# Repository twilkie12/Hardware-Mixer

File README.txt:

As a disclaimer, I am an amateur at programming and hardware design and so cannot guarantee any of this will work for you.
Will only work for Windows 10 but the hardware could easily be used with an equivalent program on Linux.
It's a bit buggy and probably not written to any decent standard but it is what it is.
This document is less of a README and more of a loose, constantly changing list of things I need to do, need to fix, want to add, need 
to look into or just think some time in the future could be interesting to look at. As such it is basically a brain dump and not
hugely important; nothing past the second paragraph will be useful for actually creating/setting up the board.
Will be adding a plastic enclosure at some point, probably 3D printed base with acrylic top.
Ask and I can send you a (possibly assembled for a fee) PCB for cost + shipping, ostensibly to test and help with prototyping but with 
no obligation to do so however any help adding to or fixing things would be appreciated.
I am open to any and all feedback.

If you decide to get the PCB manufactured yourself and put it all together yourself then some notes:

	- The Kicad board routing is currently broken because of the way I did the pours. Rebuilding it will give you a single 5V pour
	  on the top and a single GND pour on the bottom (maybe, your milage may vary). This is an issue because there is supposed to be 
	  THREE small GND zones on the top surface, one each on the right of the PIC16f15323's and one off the GND pin of the micro-usb
	  connector with a single 5V zone on the rest of the surface. I will at some stage fix this but I have already ordered the
	  boards and the file broke afterwards so it is not a top priority for me.
	- The python script looks for a specific serial number on a USB device and then trys to connect to that. You will need to use
	  a CH340B as this is allows you to change the EEPROM and write the serial number to the chip. The software and drivers to
	  do this and use CH340 chips are ahead but I will say that while the drivers are from the manufactuers site the CFG program is
	  not, with the most official looking download being from the WCH forum; and I really cannot condone downloading a random .rar
	  from unknown sources. I have not downloaded the CFG from this source instead I initially found it only on a random chinese
	  filehosting site which is probably even worse.
	  (Drivers: http://www.wch.cn/download/CH341SER_EXE.html, and the program used to configure the EEPROM:
	  http://wch.cn/index.php/bbs/thread-64449-2.html -- Called CH340CFG, there are multiple sources available through google). 
	- As a warning you ONLY want to change the serial number on the chipe, changing VID, or PID WILL make the drivers stop working
	  until you manually reassign the driver to the device, not recommended if you do not know your way around your PC.
	- You will need an Arduino, USBasp or similar to burn the Arduino bootloader to the ATMEGA 168 with Arduino IDE as well as 
	  needing a PICKIT and ZIF socket to flash the PIC's. If you are so inclined adding ISP points to the PCB to flash the PIC's
	  would be very simple and I will likely add them in the next revision.

Idea is for a board with 2 rotary encoders (tried pots, didn't really work nicely), a slide pot and 16x2 LCD screen with PCF85741 i2c
backpack used to control the windows 10 volume mixer program with hardware.

Controls 2 programs volume at a time, with the name of the active programs given on the LCD screen and the active programs changed by
pressing the rotary encoder button. Master volume is controlled by slider.

Uses Atmega 168 (could use 328 easily) with arduino to run the board with PIC16f15323's reading the rotary encoders (Fattoresaimon's
i2cencoder project, https://github.com/Fattoresaimon/i2cencoder). 

AndreMiras's pycaw library used to control Windows volume mixer (https://github.com/AndreMiras/pycaw). 

Francisco Malpartida's i2cliquidcrystal library for arduino (https://bitbucket.org/fmalpartida/new-liquidcrystal/wiki/Home) 
(Need to make sure you have the right one as there are quite a few libraries with the same names with slightly different
implementations)

Uses CH340B USB-Serial chip for it's EEPROM to allow python script to recognise board (http://www.wch.cn/products/CH340.html),
(https://lcsc.com/product-detail/USB_CH340B_C81010.html).

To do:

Biggest thing is to make LCD mount on the pcb directly rather then through floating
Remove i2c backpack and just communicate directly using pins on LCD will reduce cost and hassle
This should reduce footprint and required height of the case as well as look neater with no cables inside casing
Also could make backlight/contrast easily adjustable via mounted pots on PCB - Backlight via PWM + mosfet?

Add mounting holes to PCB
Adjust footprint of 6 pin ISP header to show pin 1
Change names on breakout header to say the pin number it is connected to
Put in solder jumpers to turn enable/disable power and data transmission indicator LED's
Label reset and calibration buttons 

Source dupont right angle 1x4 and 2x3 headers precut - possibly have 2x3 but in bulk only --Done-ish
Config file and possibly send config information to board as part of initilisation
Calibration of slide pot, button done, need to write code
Look at possibly changing usb connector to something stronger then micro b
Finalise case material and design - Clear acrylic laser cut top plate need to decide on bottom half

Python code does everything decently well, need to look at getting a lib for windows media buttons

Errors to solve/fix:

-- This seems to be fixed by using a new windows install
Exception ignored in: <bound method _compointer_base.__del__ of <POINTER(IUnknown) ptr=0x2d31688 at 3000710>>
Traceback (most recent call last):
  File "D:\Programming\Python\lib\site-packages\comtypes\__init__.py", line 918, in __del__
    self.Release()
  File "D:\Programming\Python\lib\site-packages\comtypes\__init__.py", line 1172, in Release
    return self.__com_Release()
OSError: exception: access violation writing 0x00000000
Exception ignored in: <bound method _compointer_base.__del__ of <POINTER(IUnknown) ptr=0x2d31ab0 at 3000cb0>>
Traceback (most recent call last):
  File "D:\Programming\Python\lib\site-packages\comtypes\__init__.py", line 918, in __del__
    self.Release()
  File "D:\Programming\Python\lib\site-packages\comtypes\__init__.py", line 1172, in Release
    return self.__com_Release()
OSError: exception: access violation writing 0x00000000

Seems to be some sort of issue with the ctypes attempting to write to protected memory addresses.
New pointer is being defined and put into memory every time it checks for change in sessions or change in endpoint

The serial com object sometimes has errors, need to find the error message but something about Vtable lookup, rare and also seemingly
fixed on fresh windows install

Prints: (-2004287484, None, (None, None, None, 0, None))
Need to figure out where from and why, prints it because python program prints out errors or serial coms if it gets confused

Occasionally PC doesn't decode serial input, not a big deal it tends to just ignore it and then polls again .2s later

The atmega sometimes gets stuck in a send and will stop working and just be recieving constant request markers from the PC which 
will then write to the screen -- fixed with a timeout kind of thing on both ends

Pressing reset on board takes a significant amount of time for the computer to realise and re-initilize -- Fixed?

Could possibly add PID recognition for programs, default to whatever name is already there but for some programs maybe have a list of
PIDS with names the user wants to have used, ie windows systems sounds can be void, "windowsshellexperience" or "Explorer" depending on
how windows feels on that day a list of known pids with their custom names could be made and edited by the user
Probably should check if program PID's are static or dynamic 
Process is psutil object
	--PID is dynamic but can look up the Process.exe() to see the program file for the sound stream, that should be stable

Could add play/pause, next, back buttons - Need to find python library to send windows keyboard commands and decide on how to send
those/what markers

Make a config file to have some settings in it for the program. Leave a default setting but maybe some adjustable parameters
	-- This could definitly be put into a GUI to control rgb values, backlight brightness, program name recognition etc.

RBG lighting settings could be funny, need to figure out how to send to board 
	How many lights, what type, might need to get drivers, i2c maybe too expensive, worth effort?, probably use config file
		-- Lots of spare PWM pins off IC
		-- Chuck small transistors onto the PWM pins, super cheap to get transistors in packs of 100 or whatever
		-- LED's aren't super cheap but maybe in bulk and would look pretty cool
		-- Dimming for LEDs could be an issue as well as choosing where to put them so they aren't facing up and just blinding
		   the user through the top clear plate, but also bottom of pcb currently planned to be enclosed by casing
  
 Look at getting rid of i2c backpack on LCD to cut cost, have the spare pins for it off IC and it might speed everything up although 
 that hasn't been a noticable problem yet even with only 16MHz atmega168
 		-- Using higher freq is possible with 5V I think, need to have another look at the data sheet
 
 Is current hardware debouncing good enough -- need to get into ece labs for oscills
 
 Fix PCB/schematic design errors -  it's just ugly

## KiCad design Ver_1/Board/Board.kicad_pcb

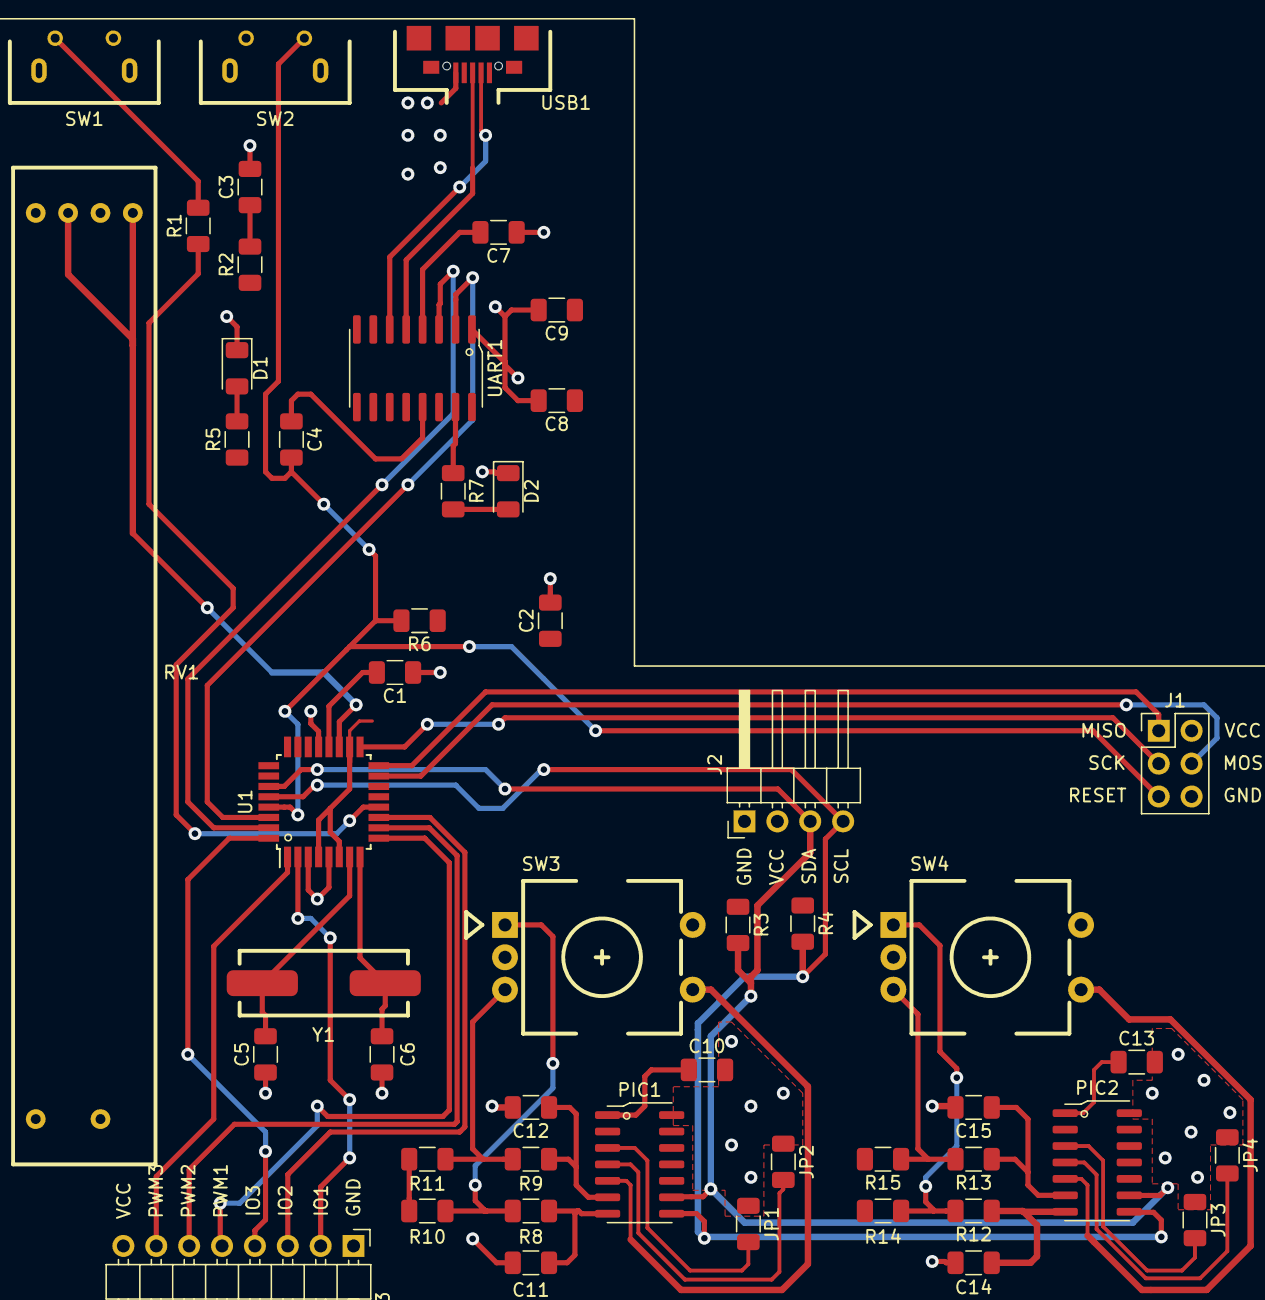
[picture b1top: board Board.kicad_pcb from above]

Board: 2 copper layers, 50 parts (0 on the bottom side), 44 nets.

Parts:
C1, C2, C3, C4, C7, C8, C10, C13: 0.1uF; C_1206_3216Metric
C5, C6: 20pF; C_1206_3216Metric
C9: 10uF; C_1206_3216Metric
C11, C12, C14, C15: 10nF; C_1206_3216Metric
D1: RED; LED_1206_3216Metric
D2: BLUE; LED_1206_3216Metric
J1: ISP Header; PinHeader_2x03_P2.54mm_Vertical
J2: LCD Header; PinHeader_1x04_P2.54mm_Horizontal
J3: Breakout; PinHeader_1x08_P2.54mm_Horizontal
JP1, JP3: ADR2; R_1206_3216Metric
JP2, JP4: ADR3; R_1206_3216Metric
PIC1, PIC2: PIC16F15323_I_SL; SOIC-14_3.9x8.7mm_P1.27mm
R1: 1k; R_1206_3216Metric
R2, R6, R8, R9, R10, R11, R12, R13, R14, R15: 10k; R_1206_3216Metric
R3, R4: 47k; R_1206_3216Metric
R5, R7: 330; R_1206_3216Metric
RV1: 10k SLIDE; Slide_potentiometer_Behringer
SW1: Calibration; Right_angle_momentary_button
SW2: Reset; Right_angle_momentary_button
SW3, SW4: Encoder; RotaryEncoder_Alps_EC11E-Switch_Vertical_H20mm
U1: ATmega168PA-AU; TQFP-32_7x7mm_P0.8mm
UART1: CH340B; SOP-16_150MIL
USB1: USB_Micro_B; Micro_B_SMD_G19
Y1: 16MHz; HC49S_SMD_Crystal

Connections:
+5V: C2.1, C8.1, C9.1, C10.1, C13.1, J1.2, J2.2, J3.8, PIC1.1, PIC2.1, R2.1, R3.1, R4.1, R5.1, R6.1, R10.1, R11.2, R14.1, R15.2, RV1.1, U1.4, U1.6, U1.18, UART1.16, USB1.1
/ADC1: RV1.2, U1.19
/CAL: R1.1, U1.12
/I2C Encoder 1/PB: PIC1.5, SW3.2
/I2C Encoder 1/RA: C11.2, PIC1.7, R8.1
/I2C Encoder 1/RB: C12.1, PIC1.6, R9.1
/I2C Encoder 2/PB: PIC2.5, SW4.2
/I2C Encoder 2/RA: C14.2, PIC2.7, R12.1
/I2C Encoder 2/RB: C15.1, PIC2.6, R13.1
/IO1: J3.2, U1.2
/IO2: J3.3, U1.11
/IO3: J3.4, U1.32
/MISO: J1.1, U1.16
/MOSI: J1.4, U1.15
/PWM1: J3.5, U1.9
/PWM2: J3.6, U1.10
/PWM3: J3.7, U1.1
/RESET: C4.2, J1.5, R6.2, SW2.1, U1.29
/SCK: J1.3, U1.17
DATA+: UART1.5, USB1.3
DATA-: UART1.6, USB1.2
DTR: C4.1, UART1.13
GND: C1.1, C2.2, C3.2, C5.1, C6.1, C7.1, C8.2, C9.2, C10.2, C11.1, C12.2, C13.2, C14.1, C15.2, D1.1, D2.1, J1.6, J2.1, J3.1, JP1.1, JP2.1, JP3.1, JP4.1, PIC1.14, PIC2.14, RV1.3, SW1.1, SW2.2, SW3.1, SW3.C, SW4.1, SW4.C, U1.3, U1.5, U1.21, UART1.1, USB1.5
unnamed: C1.2, U1.20
unnamed: C3.1, R2.2
unnamed: C5.2, U1.7, Y1.1
unnamed: C6.2, U1.8, Y1.2
unnamed: C7.2, UART1.4
unnamed: D1.2, R5.2
unnamed: D2.2, R7.2
unnamed: JP1.2, PIC1.3
unnamed: JP2.2, PIC1.4
unnamed: JP3.2, PIC2.3
unnamed: JP4.2, PIC2.4
unnamed: R1.2, SW1.2
unnamed: R7.1, UART1.15
unnamed: R8.2, R10.2, SW3.A
unnamed: R9.2, R11.1, SW3.B
unnamed: R12.2, R14.2, SW4.A
unnamed: R13.2, R15.1, SW4.B
RX: U1.31, UART1.3
SCL: J2.4, PIC1.8, PIC2.8, R4.2, U1.28
SDA: J2.3, PIC1.9, PIC2.9, R3.2, U1.27
TX: U1.30, UART1.2
